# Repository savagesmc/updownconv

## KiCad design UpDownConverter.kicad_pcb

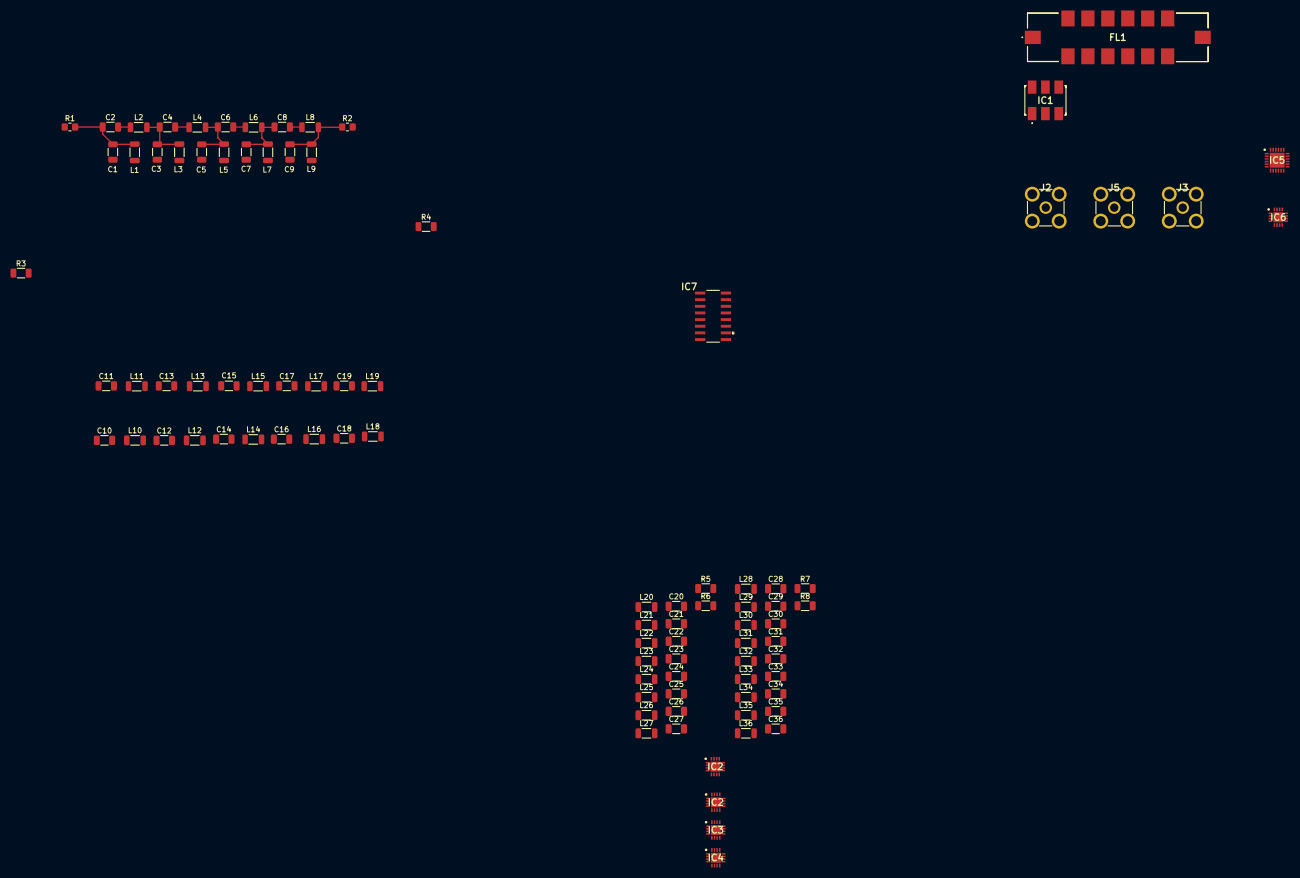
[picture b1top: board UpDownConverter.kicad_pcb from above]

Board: 4 copper layers, 92 parts (0 on the bottom side), 60 nets.

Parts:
C1, C9: 100 pF; C_1206_3216Metric
C2: 820 pf; C_1206_3216Metric
C3, C5, C7: 180 pF; C_1206_3216Metric
C4, C6: 680 pF; C_1206_3216Metric
C8: 820 pF; C_1206_3216Metric
C10, C18: 18 pF; C_1206_3216Metric
C11: 68 pf; C_1206_3216Metric
C12, C14, C16: 33 pF; C_1206_3216Metric
C13, C15: 56 pF; C_1206_3216Metric
C17: 68 pF; C_1206_3216Metric
C19, C27, C28, C36: 4.7 pF; C_1206_3216Metric
C20, C29: 6.8 pf; C_1206_3216Metric
C21, C23, C25, C30, C32, C34: 8.2 pF; C_1206_3216Metric
C22, C24, C31, C33: 5.6 pF; C_1206_3216Metric
C26, C35: 6.8 pF; C_1206_3216Metric
FL1: BPF-A410+; BPFA410
IC1: ADE-2ASK+; ADE2ASK
IC2, IC2#2, IC3, IC4, IC6: HMC1118LP3DE; QFN50P300X300X95-17N-D
IC5: ADRF5040BCPZ-R7; QFN50P400X400X90-25N-D
IC7: SN74S124D; SOIC127P600X175-16N
J2, J3, J5: PCB.SMAFRA.HT; PCBSMAFRAHT
L1, L9: 2.7 uH; L_1206_3216Metric
L2, L4, L6, L8: 330 nH; L_1206_3216Metric
L3, L5, L7: 1.5 uH; L_1206_3216Metric
L10, L18: 180 nH; L_1206_3216Metric
L11, L13, L15, L17: 56 nH; L_1206_3216Metric
L12, L14, L16: 100 nH; L_1206_3216Metric
L19, L27, L28, L36: 22 nH; L_1206_3216Metric
L20, L22, L24, L26, L29, L31, L33, L35: 15 nH; L_1206_3216Metric
L21, L23, L25, L30, L32, L34: 12 nH; L_1206_3216Metric
R1, R2: 50 Ohms; R_0805_2012Metric_Pad1.20x1.40mm_HandSolder
R3, R4, R5, R6, R7, R8: 50 Ohms; R_1206_3216Metric

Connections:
/Antenna/Antenna: IC5.3 (RFC), J3.1
/Band Select Logic/CTRL1: IC6.10 (VCTRL), IC6.11 (LS)
/Band Select Logic/CTRL2: IC2.10 (VCTRL), IC2.11 (LS)
/Band Select Logic/CTRL3: IC4.10 (VCTRL), IC4.11 (LS)
/Band Select Logic/CTRL4: IC3.10 (VCTRL), IC3.11 (LS)
/Band Select Logic/POWER1: IC2.12 (VDD), IC3.12 (VDD), IC4.12 (VDD), IC5.17 (VDD), IC6.12 (VDD)
/Band Select Logic/POWER3: IC2.9 (VSS), IC3.9 (VSS), IC4.9 (VSS), IC6.9 (VSS)
/Band Select Switch/HF_Band: IC5.23 (RF1), R1.1
/Band Select Switch/L Band Port: IC5.8 (RF4), R7.1
/Band Select Switch/UHF Band: IC5.11 (RF3), R5.1
/Band Select Switch/VHF Band: IC5.20 (RF2), R3.1
/Baseband TR Switch/Common: IC3.3 (RFC), IC6.3 (RFC)
/Baseband TR Switch/RX: IC6.14 (RF1), J5.1
/Baseband TR Switch/TX: IC6.7 (RF2), J2.1
/HF_Bandpass_Filter/HF BPF Port 2: IC2.14 (RF1), R2.2
/LBAND_Bandpass_Filter/LBand BPF Port 2: IC4.7 (RF2), R8.2
/Mixer & Band Select/Mixer_UHF: IC4.14 (RF1), R6.2
/Mixer & Band Select/Mixer_VHF: IC2.7 (RF2), R4.2
Earth: C1.2, C3.2, C5.2, C7.2, C9.2, C10.2, C12.2, C14.2, C16.2, C18.2, C19.2, C21.2, C23.2, C25.2, C27.2, C28.2, C30.2, C32.2, C34.2, C36.2, IC2#2.1 (GND_1), IC2#2.2 (GND_2), IC2#2.4 (GND_3), IC2#2.5 (GND_4), IC2#2.6 (GND_5), IC2#2.8 (GND_6), IC2#2.13 (GND_7), IC2#2.15 (GND_8), IC2#2.16 (GND_9), IC2#2.17 (GND_10), L1.2, L3.2, L5.2, L7.2, L9.2, L10.2, L12.2, L14.2, L16.2, L18.2, L19.2, L21.2, L23.2, L25.2, L27.2, L28.2, L30.2, L32.2, L34.2, L36.2
GND: FL1.2 (GROUND_1), FL1.3 (GROUND_2), FL1.4 (GROUND_3), FL1.5 (GROUND_4), FL1.6 (GROUND_5), FL1.7 (GROUND_6), FL1.9 (GROUND_7), FL1.10 (GROUND_8), FL1.11 (GROUND_9), FL1.12 (GROUND_10), FL1.13 (GROUND_11), FL1.14 (GROUND_12), IC1.1 (GROUND_1), IC1.4 (GROUND_2), IC1.5 (GROUND_3), IC2.1 (GND_1), IC2.2 (GND_2), IC2.4 (GND_3), IC2.5 (GND_4), IC2.6 (GND_5), IC2.8 (GND_6), IC2.13 (GND_7), IC2.15 (GND_8), IC2.16 (GND_9), IC2.17 (GND_10), IC3.1 (GND_1), IC3.2 (GND_2), IC3.4 (GND_3), IC3.5 (GND_4), IC3.6 (GND_5), IC3.8 (GND_6), IC3.13 (GND_7), IC3.15 (GND_8), IC3.16 (GND_9), IC3.17 (GND_10), IC4.1 (GND_1), IC4.2 (GND_2), IC4.4 (GND_3), IC4.5 (GND_4), IC4.6 (GND_5), IC4.8 (GND_6), IC4.13 (GND_7), IC4.15 (GND_8), IC4.16 (GND_9), IC4.17 (GND_10), IC5.1 (GND_1), IC5.2 (GND_2), IC5.4 (GND_3), IC5.5 (GND_4), IC5.6 (GND_5), IC5.7 (GND_6), IC5.9 (GND_7), IC5.10 (GND_8), IC5.12 (GND_9), IC5.13 (GND_10), IC5.18 (GND_11), IC5.19 (GND_12), IC5.21 (GND_13), IC5.22 (GND_14), IC5.24 (GND_15), IC5.25 (GND_16), IC6.1 (GND_1), IC6.2 (GND_2), IC6.4 (GND_3), IC6.5 (GND_4), IC6.6 (GND_5), IC6.8 (GND_6), IC6.13 (GND_7), IC6.15 (GND_8), IC6.16 (GND_9), IC6.17 (GND_10), J2.2, J2.3, J2.4, J2.5, J3.2, J3.3, J3.4, J3.5, J5.2, J5.3, J5.4, J5.5
unnamed: C1.1, C2.1, L1.1, R1.2
unnamed: C2.2, L2.1
unnamed: C3.1, C4.1, L2.2, L3.1
unnamed: C4.2, L4.1
unnamed: C5.1, C6.1, L4.2, L5.1
unnamed: C6.2, L6.1
unnamed: C7.1, C8.1, L6.2, L7.1
unnamed: C8.2, L8.1
unnamed: C9.1, L8.2, L9.1, R2.1
unnamed: C10.1, C11.1, L10.1, R3.2
unnamed: C11.2, L11.1
unnamed: C12.1, C13.1, L11.2, L12.1
unnamed: C13.2, L13.1
unnamed: C14.1, C15.1, L13.2, L14.1
unnamed: C15.2, L15.1
unnamed: C16.1, C17.1, L15.2, L16.1
unnamed: C17.2, L17.1
unnamed: C18.1, L17.2, L18.1, R4.1
unnamed: C19.1, C20.1, L19.1, R5.2
unnamed: C20.2, L20.1
unnamed: C21.1, C22.1, L20.2, L21.1
unnamed: C22.2, L22.1
unnamed: C23.1, C24.1, L22.2, L23.1
unnamed: C24.2, L24.1
unnamed: C25.1, C26.1, L24.2, L25.1
unnamed: C26.2, L26.1
unnamed: C27.1, L26.2, L27.1, R6.1
unnamed: C28.1, C29.1, L28.1, R7.2
unnamed: C29.2, L29.1
unnamed: C30.1, C31.1, L29.2, L30.1
unnamed: C31.2, L31.1
unnamed: C32.1, C33.1, L31.2, L32.1
unnamed: C33.2, L33.1
unnamed: C34.1, C35.1, L33.2, L34.1
unnamed: C35.2, L35.1
unnamed: C36.1, L35.2, L36.1, R8.1
unnamed: FL1.1 (RF_IN), IC1.2 (IF)
unnamed: FL1.8 (RF_OUT), IC3.14 (RF1)
unnamed: IC1.3 (RF), IC2.3 (RFC), IC2#2.3 (RFC)
unnamed: IC3.7 (RF2), IC4.3 (RFC)

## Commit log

2023-08-28 Initial commit.
2023-09-11 Redefined filters & Top Level Diagram
    - Implement wider filters to accomodate 10% tolerance parts.
    - Break design in to top-level heirarchical blocks.
    - Start wiring some of the blocks together.
    - Add L-Band segment, but is currently just a copy of the UHF filter.
    - Add the start of a TX path.
    - Add placeholders for power and band/tune control.
2023-09-18 More filter work. Add project title to drawings.
2023-10-08 Major restructure. Add power/control busses.
2023-10-09 Add some of the routing for the power signals.
2023-10-09 Replace DDS with VCOs + a switch.
